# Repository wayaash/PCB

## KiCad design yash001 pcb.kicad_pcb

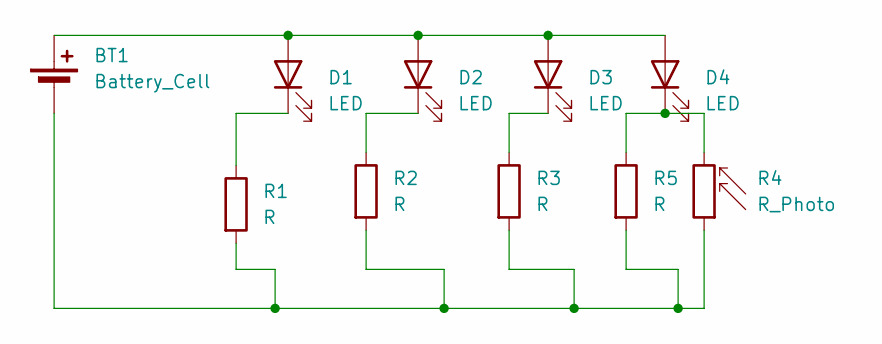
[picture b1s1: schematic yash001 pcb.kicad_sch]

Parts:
BT1: Battery_Cell; BatteryHolder_Keystone_3034_1x20mm
D1, D2, D3, D4: LED; LED_D5.0mm
R1, R2, R3, R5: R; R_Axial_DIN0207_L6.3mm_D2.5mm_P7.62mm_Horizontal
R4: R_Photo; R_LDR_5.1x4.3mm_P3.4mm_Vertical

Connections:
unnamed: BT1.1 (+), D1.2 (A), D2.2 (A), D3.2 (A), D4.2 (A)
unnamed: BT1.2 (-), R1.2, R2.2, R3.2, R4.1, R5.2
unnamed: D1.1 (K), R1.1
unnamed: D2.1 (K), R2.1
unnamed: D3.1 (K), R3.1
unnamed: D4.1 (K), R4.2, R5.1

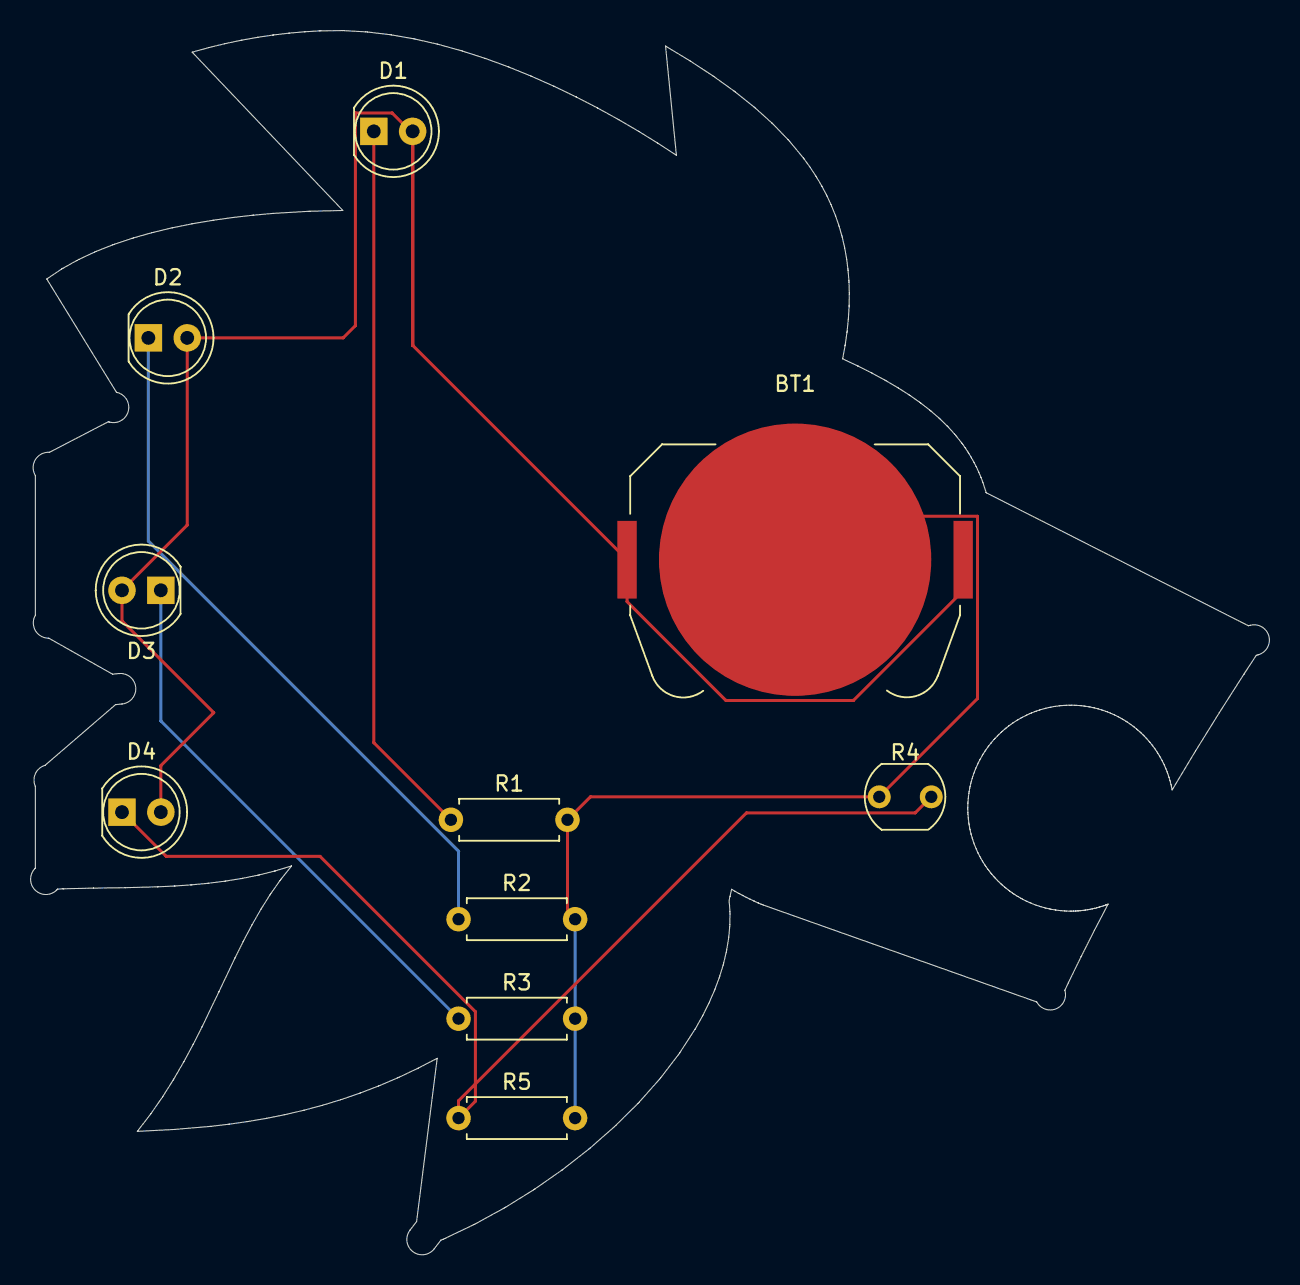
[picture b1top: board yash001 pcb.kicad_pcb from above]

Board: 2 copper layers, 81.0 x 80.0 mm, 10 parts (0 on the bottom side), 6 nets.

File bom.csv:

Designator,Footprint,Quantity,Value,LCSC Part #
BT1,BatteryHolder_Keystone_3034_1x20mm,1,Battery_Cell,
"D1, D2, D3, D4",LED_D5.0mm,4,LED,
"R1, R2, R3, R5",R_Axial_DIN0207_L6.3mm_D2.5mm_P7.62mm_Horizontal,4,R,
R4,R_LDR_5.1x4.3mm_P3.4mm_Vertical,1,R_Photo,
